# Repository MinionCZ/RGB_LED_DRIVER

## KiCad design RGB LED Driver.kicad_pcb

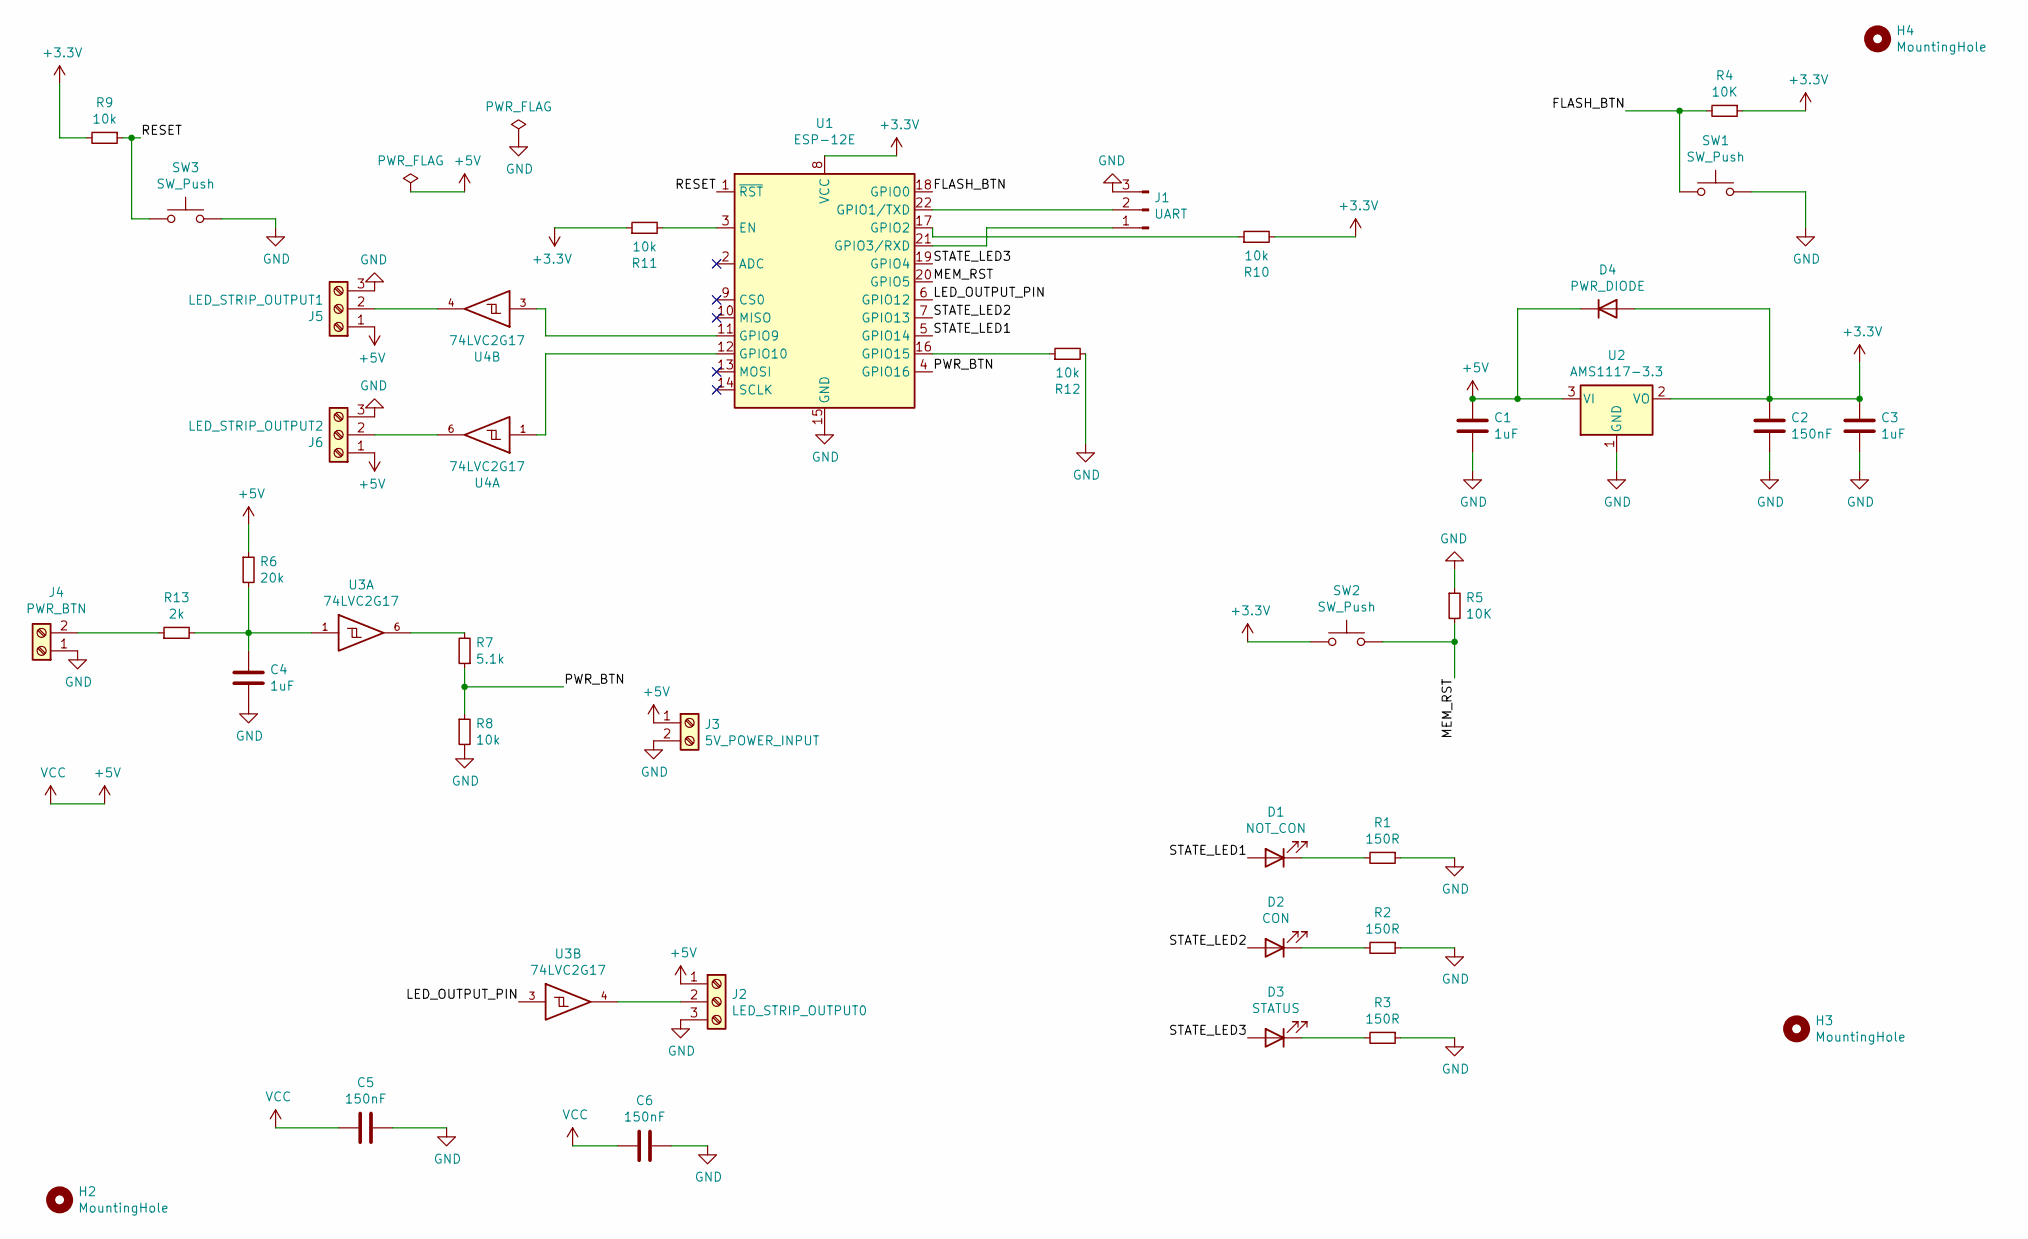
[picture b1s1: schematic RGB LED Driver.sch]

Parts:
C1, C3, C4: 1uF; C_1206_3216Metric_Pad1.33x1.80mm_HandSolder
C2, C5, C6: 150nF; C_0805_2012Metric_Pad1.18x1.45mm_HandSolder
D1: NOT_CON; LED_0805_2012Metric_Pad1.15x1.40mm_HandSolder
D2: CON; LED_0805_2012Metric_Pad1.15x1.40mm_HandSolder
D3: STATUS; LED_0805_2012Metric_Pad1.15x1.40mm_HandSolder
D4: PWR_DIODE; D_MiniMELF_Handsoldering
H2, H3, H4: MountingHole; MountingHole_3.2mm_M3
J1: UART; PinSocket_1x03_P2.54mm_Vertical
J2: LED_STRIP_OUTPUT0; TerminalBlock_Altech_AK300-3_P5.00mm
J3: 5V_POWER_INPUT; TerminalBlock_Altech_AK300-2_P5.00mm
J4: PWR_BTN; TerminalBlock_Altech_AK300-2_P5.00mm
J5: LED_STRIP_OUTPUT1; TerminalBlock_Altech_AK300-3_P5.00mm
J6: LED_STRIP_OUTPUT2; TerminalBlock_Altech_AK300-3_P5.00mm
R1, R2, R3: 150R; R_0805_2012Metric_Pad1.20x1.40mm_HandSolder
R4, R5: 10K; R_0805_2012Metric_Pad1.20x1.40mm_HandSolder
R6: 20k; R_0805_2012Metric_Pad1.20x1.40mm_HandSolder
R7: 5.1k; R_0805_2012Metric_Pad1.20x1.40mm_HandSolder
R8, R9, R10, R11, R12: 10k; R_0805_2012Metric_Pad1.20x1.40mm_HandSolder
R13: 2k; R_0805_2012Metric_Pad1.20x1.40mm_HandSolder
SW1, SW2, SW3: SW_Push; SW_Push_1P1T_NO_6x6mm_H9.5mm
U1: ESP-12E
U2: AMS1117-3.3; SOT-223-3_TabPin2
U3, U4: 74LVC2G17; SOT-23-6_Handsoldering

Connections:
+3V3: C2.1, C3.1, D4.2 (A), R4.1, R9.2, R10.2, R11.1, SW2.1, U1.8 (VCC), U2.2 (VO)
+5V: C1.1, C5.2, C6.2, D4.1 (K), J2.1, J3.1, J5.1, J6.1, R6.1, U2.3 (VI), U3.5 (VCC), U4.5 (VCC)
/FLASH_BTN: R4.2, SW1.1, U1.18 (GPIO0)
/LED_OUTPUT_PIN: U1.6 (GPIO12), U3.3
/MEM_RST: R5.2, SW2.2, U1.20 (GPIO5)
/PWR_BTN: R7.1, R8.1, U1.4 (GPIO16)
/RESET: R9.1, SW3.1, U1.1 (~RST)
/STATE_LED1: D1.2 (A), U1.5 (GPIO14)
/STATE_LED2: D2.2 (A), U1.7 (GPIO13)
/STATE_LED3: D3.2 (A), U1.19 (GPIO4)
GND: C1.2, C2.2, C3.2, C4.2, C5.1, C6.1, J1.3, J2.3, J3.2, J4.1, J5.3, J6.3, R1.1, R2.1, R3.1, R5.1, R8.2, R12.2, SW1.2, SW3.2, U1.15 (GND), U2.1 (GND), U3.2 (GND), U4.2 (GND)
unnamed: C4.1, R6.2, R13.2, U3.1
unnamed: D1.1 (K), R1.2
unnamed: D2.1 (K), R2.2
unnamed: D3.1 (K), R3.2
unnamed: J1.1, U1.21 (GPIO3/RXD)
unnamed: J1.2, U1.22 (GPIO1/TXD)
unnamed: J2.2, U3.4
unnamed: J4.2, R13.1
unnamed: J5.2, U4.4
unnamed: J6.2, U4.6
unnamed: R7.2, U3.6
unnamed: R10.1, U1.17 (GPIO2)
unnamed: R11.2, U1.3 (EN)
unnamed: R12.1, U1.16 (GPIO15)
unnamed: U1.11 (GPIO9), U4.3
unnamed: U1.12 (GPIO10), U4.1

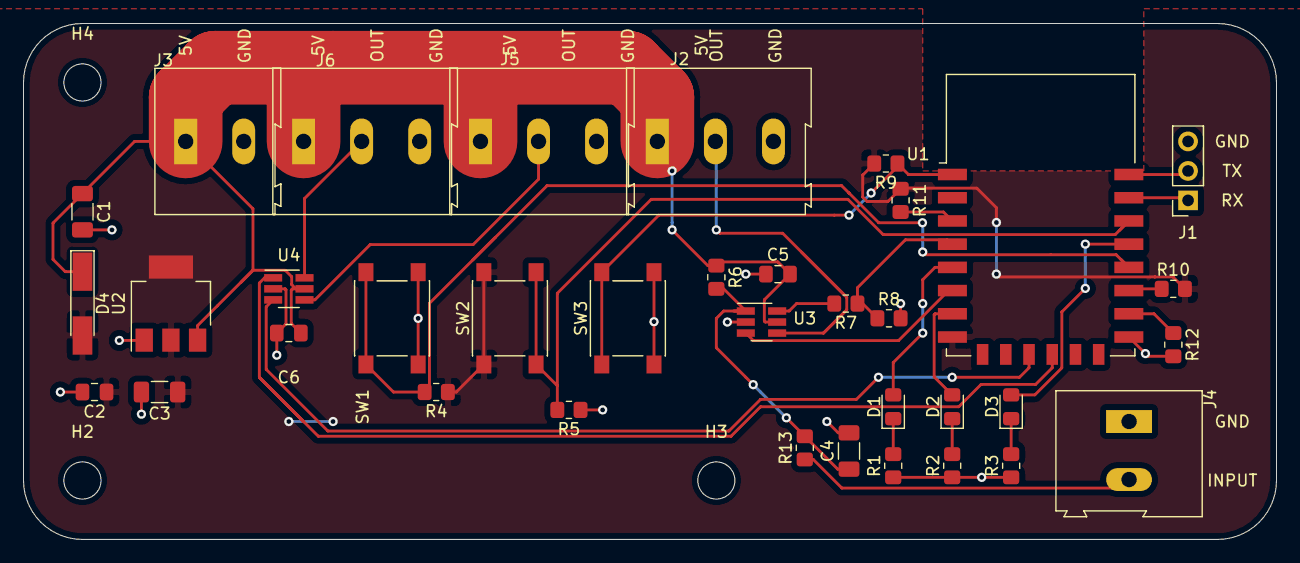
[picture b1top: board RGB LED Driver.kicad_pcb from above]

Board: 2 copper layers, 108.0 x 44.4 mm, 39 parts (0 on the bottom side), 27 nets.

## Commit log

2021-04-05 Initial commit with complete schematic and set components to footprints
2021-04-05 Working on PCB, bad footprint needs to be reworked
2021-04-06 Done 1st version of PCB
2021-04-09 Schematic repaired and added 4 mounting holes + new 74lvc2g17
2021-04-09 PCB done, and ready for feedback
2021-04-10 PCB updated and fixed problems
2021-04-10 PCB updated, and repaired problem with via on pads
2021-04-10 PCB updated and screw terminals moved
